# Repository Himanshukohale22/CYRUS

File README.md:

# Thrust Vector Control Rockets
---

This repository contains hardware files,specifcation of board,firmware/software of Thrust vector control model Rocketry. this project is open source can be used as and update as required.

SPECIFICATION OF TVC FLIGHT COMPUTER:
---
* small flight computer board 8.2*5 cm .
* stm32f4xc on board micro-controller 
  *   ARM ®32-bit Cortex M4 CPU with FPU
  *   Adaptive real-time accelerator allowing 0-wait state execution
  *   Up to 512 Kbytes of Flash memory 128 Kbytes of SRAM
  *   operating frequency of 100MHz.

* Board power supply 
  * usb b micro (mobile charger).
  *  exteral JSt connector (12v battery).
* Sensors 
  * barometer (BMP280).
  * gyroscope & accelerometer (MPU6050). 
  * sd card 
  * rf (NRF24L)

* Digital-output triple-axis accelerometer  
* A programmable full scale rangeof ±2g,±4g,±8g and ±16g. 6-axis (DOF)accelerometer 
* Gyroscop Digital-output  X-,  Y-, z-axis
* Angular rate sensors with user-programmable full-scale range of ±250, ±500, ±1000, and ±2000°/sec.
* BMP280: pressure and altitude unit

Schematics 
---

main sheet

extra sheet

FRONT SIDE 
---

BACK SIDE

PROTOTYPE:
---

simulator/manufacturing :
---

TOOLS & REFERENCE:
---
> [kicad](https://www.kicad.org/)

> [stm32cubeIDE](https://www.st.com/en/development-tools/stm32cubeide.html)

> [stm32f411](https://www.st.com/resource/en/datasheet/stm32f411re.pdf)

> [MPU6050](https://invensense.tdk.com/wp-content/uploads/2015/02/MPU-6000-Datasheet1.pdf)

> [BMP280](https://cdn-shop.adafruit.com/datasheets/BST-BMP280-DS001-11.pdf)

> [NRF24](https://www.sparkfun.com/datasheets/Components/SMD/nRF24L01Pluss_Preliminary_Product_Specification_v1_0.pdf)

> [BUILTIN MICRO SD CARD](https://components101.com/modules/micro-sd-card-module-pinout-features-datasheet-alternatives)

> [NRFZ44N](https://pdf1.alldatasheet.com/datasheet-pdf/view/17807/PHILIPS/IRFZ44N.html)

FUTURE WORK:
---

* High speed on board microcontroller (f7,f8)
* High precision and accuracy IMU and BAROMETER 
* communication update.
* stabilizer servo module (3D printed files).

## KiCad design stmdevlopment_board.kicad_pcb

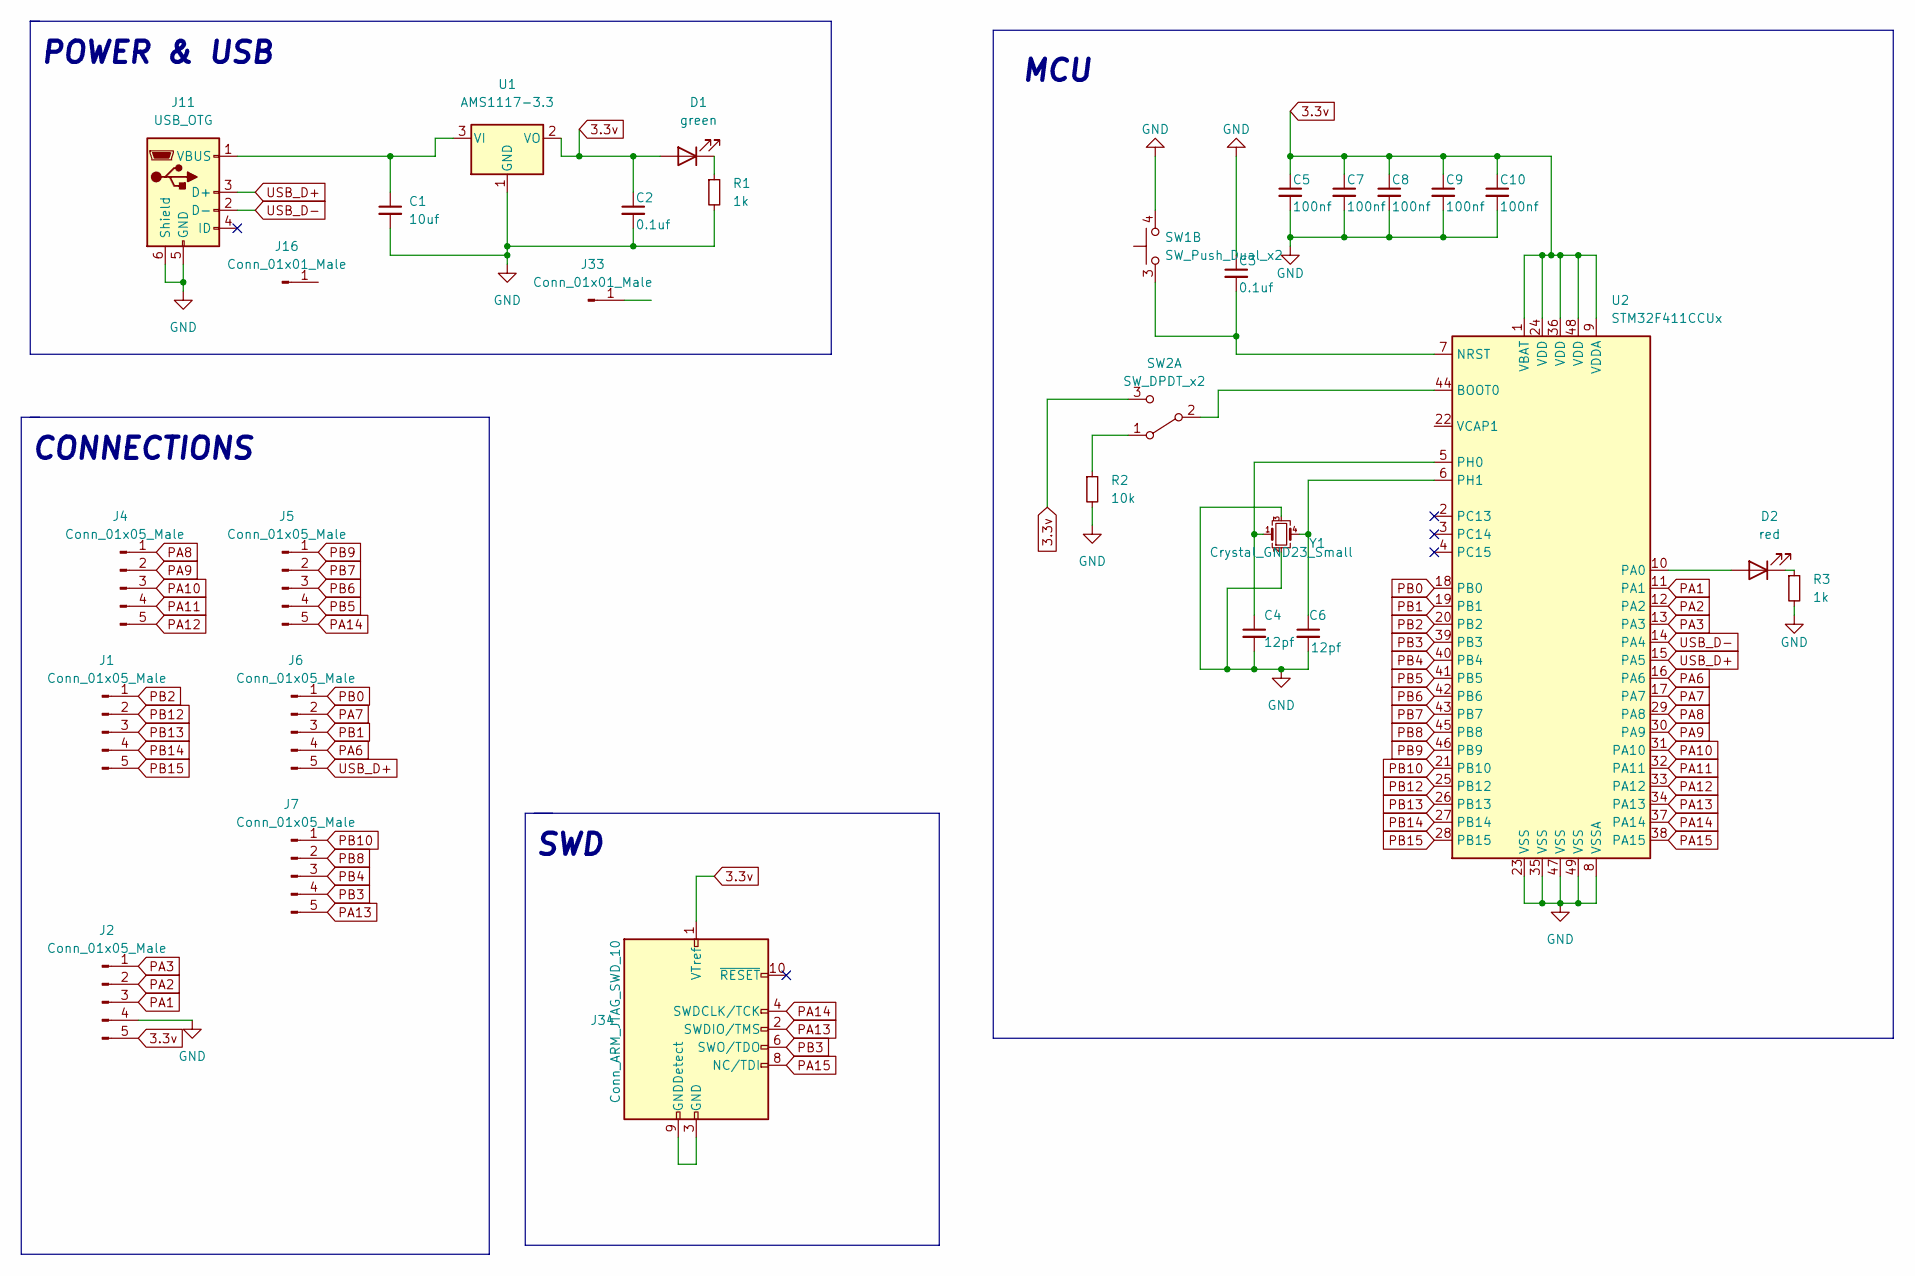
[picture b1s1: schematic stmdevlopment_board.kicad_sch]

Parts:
C1: 10uf; CP_Elec_4x3.9
C2, C3: 0.1uf; C_0603_1608Metric_Pad1.08x0.95mm_HandSolder
C4, C6: 12pf; C_0603_1608Metric_Pad1.08x0.95mm_HandSolder
C5, C7, C8, C9, C10: 100nf; C_0603_1608Metric_Pad1.08x0.95mm_HandSolder
D1: green; LED_0805_2012Metric_Pad1.15x1.40mm_HandSolder
D2: red; LED_0805_2012Metric_Pad1.15x1.40mm_HandSolder
J1, J2, J4, J5, J6, J7: Conn_01x05_Male; PinHeader_1x05_P2.54mm_Vertical
J11: USB_OTG; USB_Micro-B_Molex_47346-0001
J16, J33: Conn_01x01_Male; PinHeader_1x01_P2.54mm_Vertical
J34: Conn_ARM_JTAG_SWD_10; Tag-Connect_TC2050-IDC-NL_2x05_P1.27mm_Vertical
R1, R3: 1k; R_0603_1608Metric_Pad0.98x0.95mm_HandSolder
R2: 10k; R_0805_2012Metric_Pad1.20x1.40mm_HandSolder
SW1: SW_Push_Dual_x2; Panasonic_EVQPUJ_EVQPUA
SW2: SW_DPDT_x2; SW_CuK_JS202011CQN_DPDT_Straight
U1: AMS1117-3.3; SOT-223-3_TabPin2
U2: STM32F411CCUx; QFN-48-1EP_7x7mm_P0.5mm_EP5.6x5.6mm
Y1: Crystal_GND23_Small; Crystal_SMD_EuroQuartz_MT-4Pin_3.2x2.5mm

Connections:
3.3v: C2.1, C5.1, C7.1, C8.1, C9.1, C10.1, D1.2 (A), J2.5, J34.1 (VTref), SW2.3 (C), U1.2 (VO), U2.1 (VBAT), U2.9 (VDDA), U2.24 (VDD), U2.36 (VDD), U2.48 (VDD)
GND: C1.2, C2.2, C3.1, C4.2, C5.2, C6.2, C7.2, C8.2, C9.2, C10.2, J2.4, J11.5 (GND), J11.6 (Shield), R1.2, R2.2, R3.2, SW1.4 (D), U1.1 (GND), U2.8 (VSSA), U2.23 (VSS), U2.35 (VSS), U2.47 (VSS), U2.49 (VSS), Y1.2, Y1.3
unnamed: C1.1, J11.1 (VBUS), U1.3 (VI)
unnamed: C3.2, SW1.3 (C), U2.7 (NRST)
unnamed: C4.1, U2.5 (PH0), Y1.1
unnamed: C6.1, U2.6 (PH1), Y1.4
unnamed: D1.1 (K), R1.1
unnamed: D2.1 (K), R3.1
unnamed: D2.2 (A), U2.10 (PA0)
unnamed: J34.3 (GND), J34.5 (GND), J34.9 (GNDDetect)
unnamed: R2.1, SW2.1 (A)
unnamed: SW2.2 (B), U2.44 (BOOT0)
PA1: J2.3, U2.11 (PA1)
PA2: J2.2, U2.12 (PA2)
PA3: J2.1, U2.13 (PA3)
PA6: J6.4, U2.16 (PA6)
PA7: J6.2, U2.17 (PA7)
PA8: J4.1, U2.29 (PA8)
PA9: J4.2, U2.30 (PA9)
PA10: J4.3, U2.31 (PA10)
PA11: J4.4, U2.32 (PA11)
PA12: J4.5, U2.33 (PA12)
PA13: J7.5, J34.2 (SWDIO/TMS), U2.34 (PA13)
PA14: J5.5, J34.4 (SWDCLK/TCK), U2.37 (PA14)
PA15: J34.8 (NC/TDI), U2.38 (PA15)
PB0: J6.1, U2.18 (PB0)
PB1: J6.3, U2.19 (PB1)
PB2: J1.1, U2.20 (PB2)
PB3: J7.4, J34.6 (SWO/TDO), U2.39 (PB3)
PB4: J7.3, U2.40 (PB4)
PB5: J5.4, U2.41 (PB5)
PB6: J5.3, U2.42 (PB6)
PB7: J5.2, U2.43 (PB7)
PB8: J7.2, U2.45 (PB8)
PB9: J5.1, U2.46 (PB9)
PB10: J7.1, U2.21 (PB10)
PB12: J1.2, U2.25 (PB12)
PB13: J1.3, U2.26 (PB13)
PB14: J1.4, U2.27 (PB14)
PB15: J1.5, U2.28 (PB15)
USB_D+: J6.5, J11.3 (D+), U2.15 (PA5)
USB_D-: J11.2 (D-), U2.14 (PA4)

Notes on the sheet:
MCU
CONNECTIONS
POWER & USB
SWD

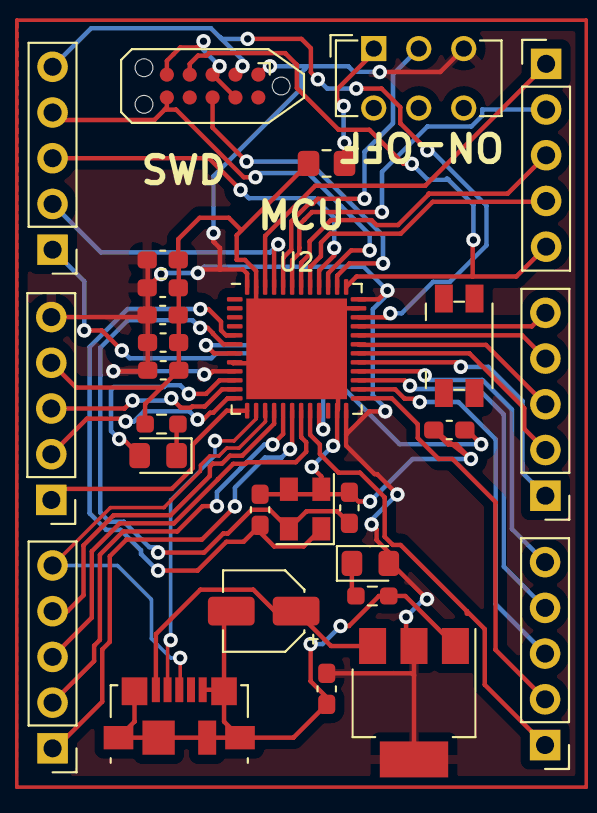
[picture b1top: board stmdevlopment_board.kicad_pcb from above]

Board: 2 copper layers, 28 parts (0 on the bottom side), 42 nets.

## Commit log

2023-04-26 initial
2023-04-30 to update
2023-05-08 Create screenshots
